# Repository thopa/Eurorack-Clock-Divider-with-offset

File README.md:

# Eurorack-Clock-Divider-with-offset
2 channel Eurorack Clock Divider with offset. Modified code from the Ardcore

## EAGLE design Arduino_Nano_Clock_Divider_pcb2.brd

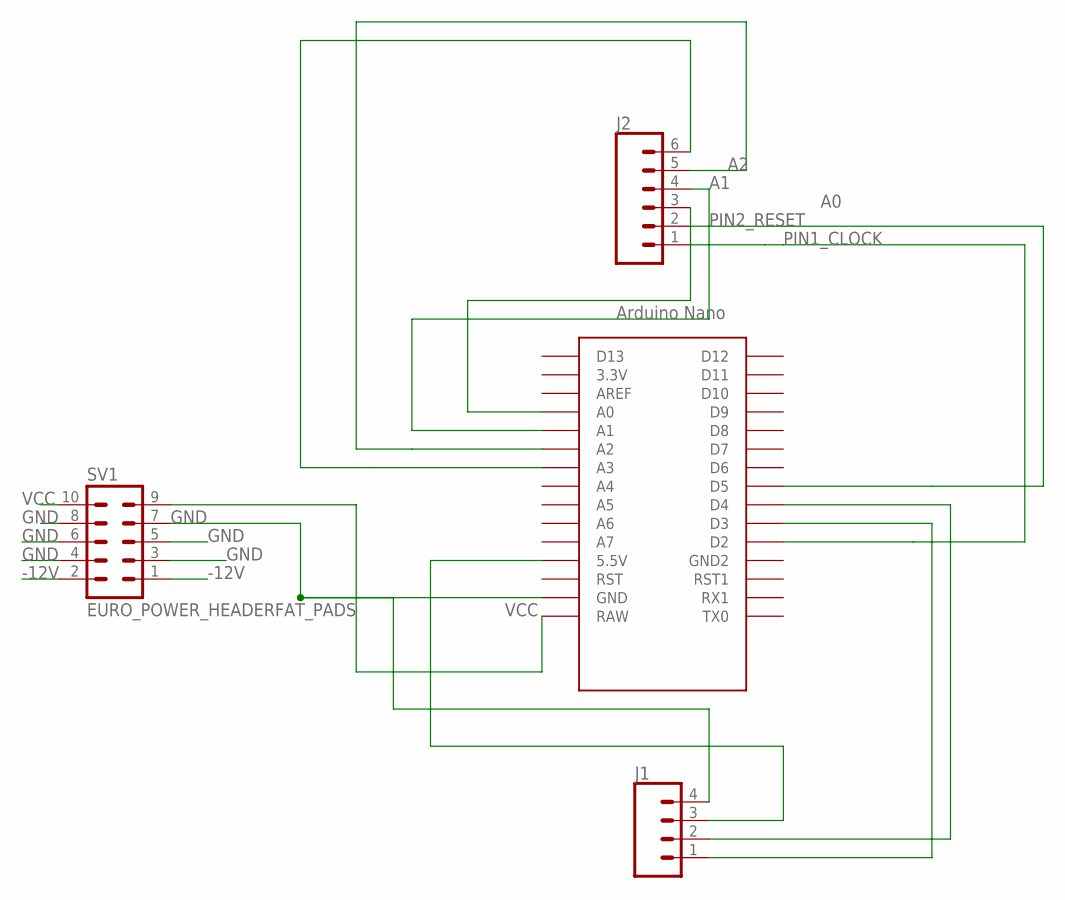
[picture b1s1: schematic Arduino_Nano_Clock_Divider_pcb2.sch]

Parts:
J1: CONN_04LONGPADS; 1X04_LONGPADS
J2: CONN_06LONGPADS; 1X06_LONGPADS
SV1: EURO_POWER_HEADERFAT_PADS; EURO_PWR_HEADER_FAT
U$1: NANO

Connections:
-12V: SV1.1, SV1.2
A0: J2.3, U$1.A0
A1: J2.4, U$1.A1
A2: J2.5, U$1.A2
A3: J2.6, U$1.A3
D3: J1.1, U$1.D3
GND: J1.4, SV1.3, SV1.4, SV1.5, SV1.6, SV1.7, SV1.8, U$1.GND
unnamed: J1.3, U$1.5V (5.5V)
unnamed: J1.2, U$1.D4
PIN1_CLOCK: J2.1, U$1.D2
PIN2_RESET: J2.2, U$1.D5
VCC: SV1.9, SV1.10, U$1.RAW

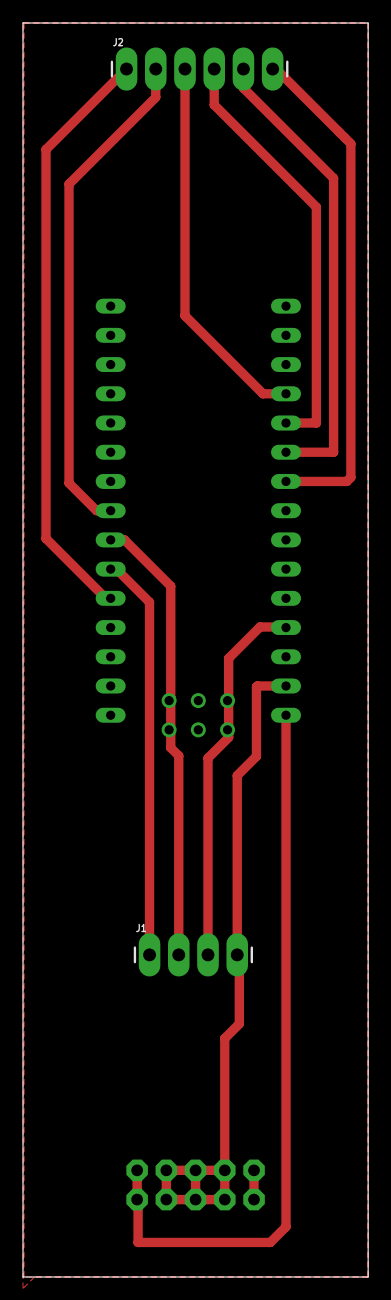
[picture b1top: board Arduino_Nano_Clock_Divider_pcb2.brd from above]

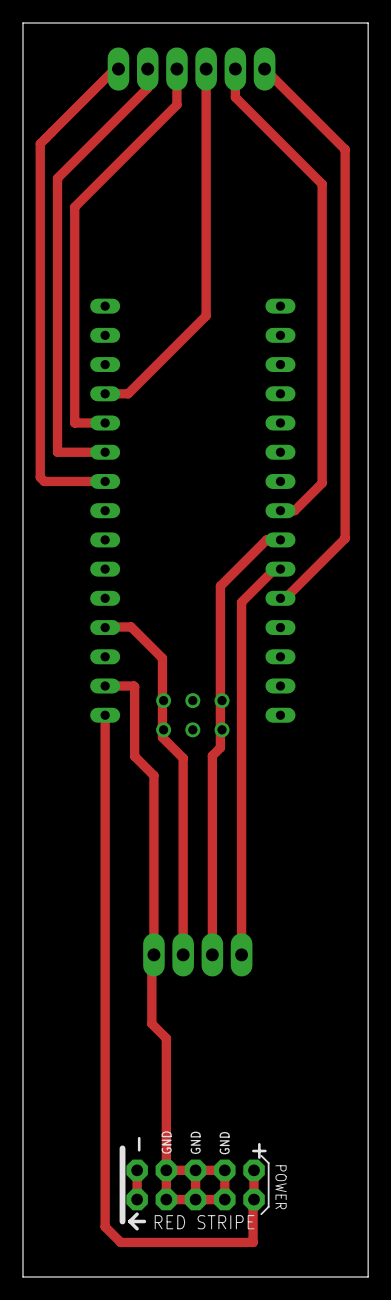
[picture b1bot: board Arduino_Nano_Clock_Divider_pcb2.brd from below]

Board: 2 copper layers, 30.0 x 109.0 mm, 4 parts (2 on the bottom side), 12 nets.

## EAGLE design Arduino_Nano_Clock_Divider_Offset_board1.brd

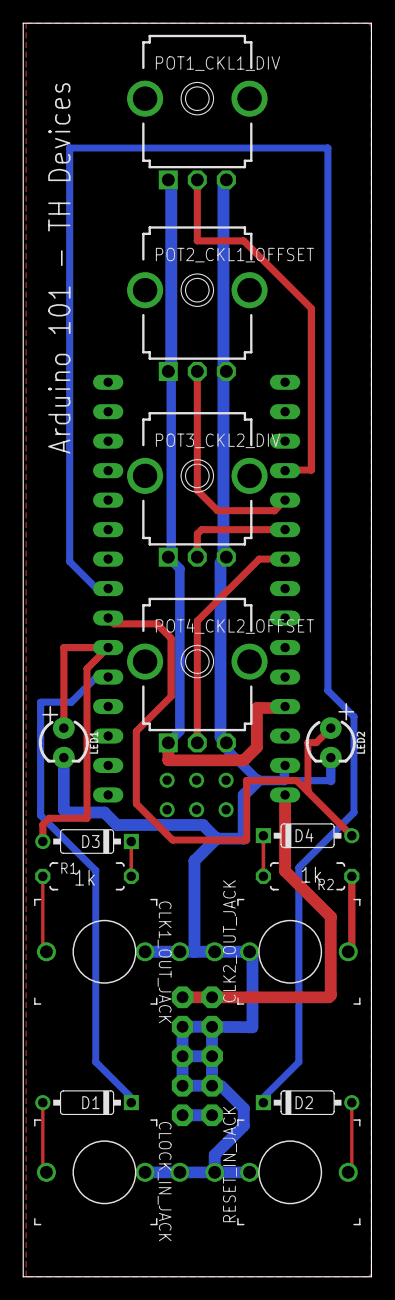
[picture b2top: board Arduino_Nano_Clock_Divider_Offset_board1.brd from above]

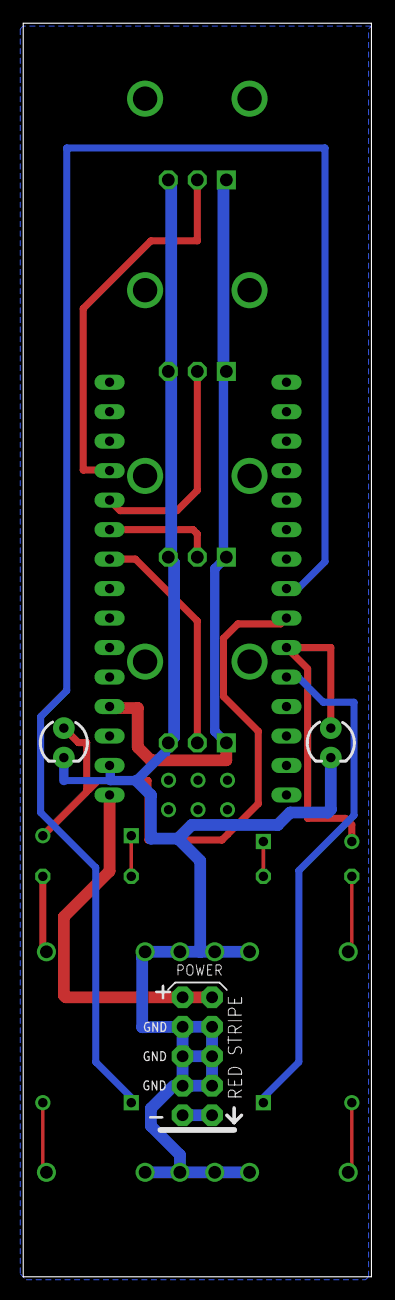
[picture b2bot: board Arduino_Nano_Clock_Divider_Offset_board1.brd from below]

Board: 2 copper layers, 30.0 x 108.0 mm, 18 parts (2 on the bottom side), 18 nets.

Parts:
CLK1_OUT_JACK, CLK2_OUT_JACK: THONKICONNNEW; WQP-PJ301M-12_JACK
CLOCK_IN_JACK: THONKICONNNEW; WQP-PJ301M-12_JACK
D1, D2, D3, D4: 1N4148; DO35-7
LED1, LED2: LED_3MM
POT1_CKL1_DIV, POT2_CKL1_OFFSET, POT3_CKL2_DIV, POT4_CKL2_OFFSET: 100k; 9MM_SNAP-IN_POT
R1, R2: 1k; 7MM_RESISTOR
RESET_IN_JACK: THONKICONNNEW; WQP-PJ301M-12_JACK
SV1: EURO_POWER_HEADERFAT_PADS; EURO_PWR_HEADER_FAT
U$1: NANO

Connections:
-12V: SV1.1, SV1.2
ARDUINO_+5V: POT1_CKL1_DIV.1, POT2_CKL1_OFFSET.1, POT3_CKL2_DIV.1, POT4_CKL2_OFFSET.1, U$1.5V
ARDUINO_A0: POT1_CKL1_DIV.2, U$1.A0
ARDUINO_A1: POT2_CKL1_OFFSET.2, U$1.A1
ARDUINO_A2: POT3_CKL2_DIV.2, U$1.A2
ARDUINO_A3: POT4_CKL2_OFFSET.2, U$1.A3
ARDUINO_CLK_IN: D1.C, U$1.D2
ARDUINO_D0: D3.A, LED1.A, U$1.D3
ARDUINO_D1: D4.A, LED2.A, U$1.D4
ARDUINO_RST_IN: D2.C, U$1.D5
CLOCK_IN_ARD: CLOCK_IN_JACK.P$1_TIP, D1.A
GND: CLK1_OUT_JACK.P$2_SWITCH, CLK1_OUT_JACK.P$3_SLEEVE, CLK2_OUT_JACK.P$2_SWITCH, CLK2_OUT_JACK.P$3_SLEEVE, CLOCK_IN_JACK.P$2_SWITCH, CLOCK_IN_JACK.P$3_SLEEVE, LED1.K, LED2.K, POT1_CKL1_DIV.3, POT2_CKL1_OFFSET.3, POT3_CKL2_DIV.3, POT4_CKL2_OFFSET.3, RESET_IN_JACK.P$2_SWITCH, RESET_IN_JACK.P$3_SLEEVE, SV1.3, SV1.4, SV1.5, SV1.6, SV1.7, SV1.8, U$1.GND
unnamed: D2.A, RESET_IN_JACK.P$1_TIP
unnamed: D3.C, R1.2
unnamed: D4.C, R2.2
unnamed: CLK2_OUT_JACK.P$1_TIP, R2.1
unnamed: CLK1_OUT_JACK.P$1_TIP, R1.1
VCC: SV1.9, SV1.10, U$1.RAW

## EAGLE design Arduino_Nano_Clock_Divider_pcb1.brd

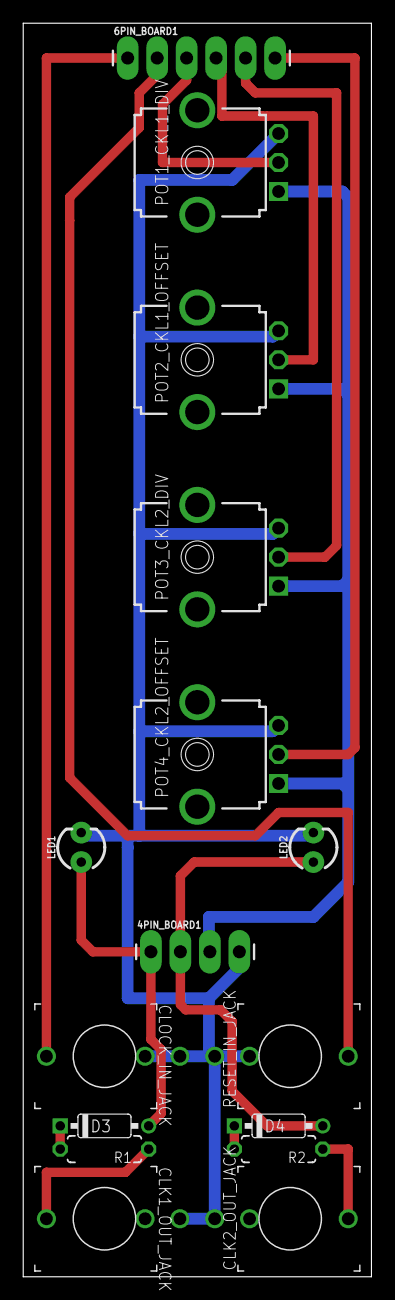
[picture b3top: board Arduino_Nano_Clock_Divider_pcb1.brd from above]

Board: 2 copper layers, 30.0 x 108.0 mm, 16 parts (0 on the bottom side), 14 nets.

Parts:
4PIN_BOARD1: 1X04_LONGPADS
6PIN_BOARD1: 1X06_LONGPADS
CLK1_OUT_JACK, CLK2_OUT_JACK: THONKICONNNEW; WQP-PJ301M-12_JACK
CLOCK_IN_JACK: THONKICONNNEW; WQP-PJ301M-12_JACK
D3, D4: 1N4148; DO35-7
LED1, LED2: LED_3MM
POT1_CKL1_DIV, POT2_CKL1_OFFSET, POT3_CKL2_DIV, POT4_CKL2_OFFSET: 100k; 9MM_SNAP-IN_POT
R1, R2: 1k; 7MM_RESISTOR
RESET_IN_JACK: THONKICONNNEW; WQP-PJ301M-12_JACK

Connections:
+5VARDUINO: 4PIN_BOARD1.3, POT1_CKL1_DIV.1, POT2_CKL1_OFFSET.1, POT3_CKL2_DIV.1, POT4_CKL2_OFFSET.1
D0: 4PIN_BOARD1.1, D3.A, LED1.A
D1: 4PIN_BOARD1.2, D4.A, LED2.A
GND_ARDUINO: 4PIN_BOARD1.4, CLK1_OUT_JACK.P$3_SLEEVE, CLK2_OUT_JACK.P$3_SLEEVE, CLOCK_IN_JACK.P$2_SWITCH, CLOCK_IN_JACK.P$3_SLEEVE, LED1.K, LED2.K, POT1_CKL1_DIV.3, POT2_CKL1_OFFSET.3, POT3_CKL2_DIV.3, POT4_CKL2_OFFSET.3, RESET_IN_JACK.P$2_SWITCH, RESET_IN_JACK.P$3_SLEEVE
unnamed: 6PIN_BOARD1.1, CLOCK_IN_JACK.P$1_TIP
unnamed: 6PIN_BOARD1.2, RESET_IN_JACK.P$1_TIP
unnamed: D3.C, R1.2
unnamed: D4.C, R2.2
unnamed: 6PIN_BOARD1.3, POT1_CKL1_DIV.2
unnamed: 6PIN_BOARD1.4, POT2_CKL1_OFFSET.2
unnamed: 6PIN_BOARD1.5, POT3_CKL2_DIV.2
unnamed: 6PIN_BOARD1.6, POT4_CKL2_OFFSET.2
unnamed: CLK2_OUT_JACK.P$1_TIP, R2.1
unnamed: CLK1_OUT_JACK.P$1_TIP, R1.1

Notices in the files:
parts and their libraries:
SparkFun-LED: Licensing: Creative Commons ShareAlike 4.0 International - https://creativecommons.org/licenses/by-sa/4.0
